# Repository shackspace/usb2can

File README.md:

usb2can
=======

Ein Adapter von USB auf CAn

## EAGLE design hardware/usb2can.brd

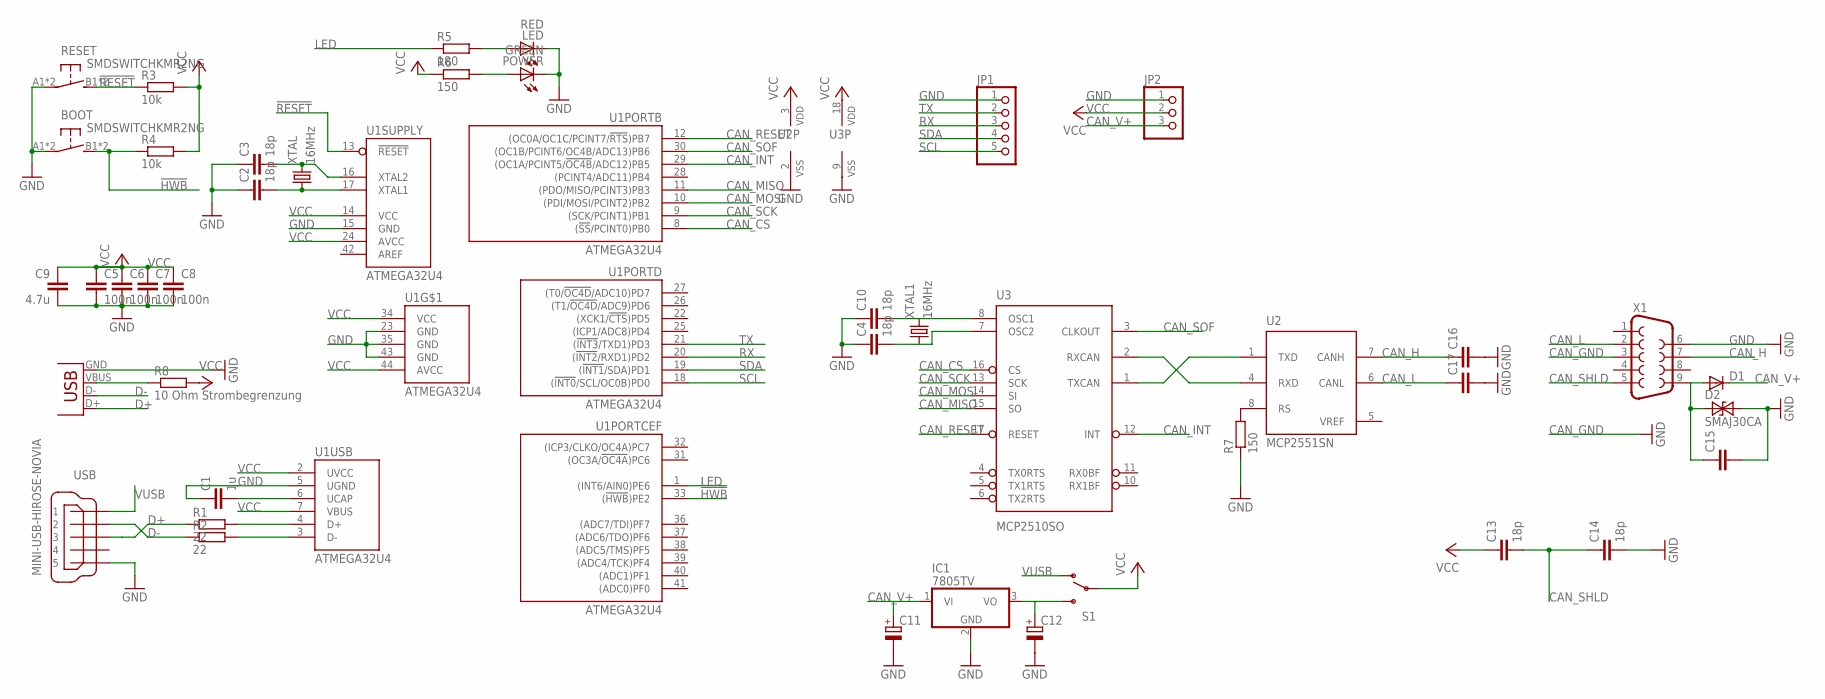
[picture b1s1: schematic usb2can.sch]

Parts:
BOOT: SMDSWITCHKMR2NG; KMR2NG
C1: 1u; C0603
C2, C3, C4, C10, C13, C14: 18p; C0603
C5, C6, C7, C8: 100n; C0603
C9: 4.7u; C0805K
C11, C12: CPOL-EU140CLH-1010; 140CLH-1010
C15, C16, C17: C-EUC0603; C0603
D1: DIODESOD; SOD-323
D2: SMAJ30CA; DO214AC
IC1: 7805TV; TO220V
JP1: PINHD-1X5; 1X05
JP2: PINHD-1X3; 1X03
LED: RED; CHIPLED_0805
POWER: GREEN; CHIPLED_0805
R1, R2: 22; R0603
R3, R4: 10k; R0603
R5: 180; R0603
R6, R7: 150; R0603
R8: 10 Ohm Strombegrenzung; R0603
RESET: SMDSWITCHKMR2NG; KMR2NG
S1: SWITCH-SPSTSMD2; SWITCH-SPDT-SMD
U1: ATMEGA32U4; TQFP44
U2: MCP2551SN; SO-08
U3: MCP2510SO; SO-18W
USB: MINI-USB-HIROSE-NOVIA; SMD-HIROSE-NOVIA
X1: F09D
X2: USB-A-S
XTAL, XTAL1: 16MHz; ABM7

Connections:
!HWB: BOOT.B1 (S), BOOT.B2 (S), R4.1, U1.33 ((!HWB!)PE2)
!RESET: R3.1, RESET.B1 (S), RESET.B2 (S), U1.13 (!RESET)
AREF: U1.42 (AREF)
CAN_CS: U1.8 ((!SS!/PCINT0)PB0), U3.16 (CS)
CAN_GND: X1.3
CAN_H: C16.1, U2.7 (CANH), X1.7
CAN_INT: U1.29 ((OC1A/PCINT5/!OC4B!/ADC12)PB5), U3.12 (INT)
CAN_L: C17.1, U2.6 (CANL), X1.2
CAN_MISO: U1.11 ((PDO/MISO/PCINT3)PB3), U3.15 (SO)
CAN_MOSI: U1.10 ((PDI/MOSI/PCINT2)PB2), U3.14 (SI)
CAN_RESET: U1.12 ((OC0A/OC1C/PCINT7/!RTS!)PB7), U3.17 (RESET)
CAN_SCK: U1.9 ((SCK/PCINT1)PB1), U3.13 (SCK)
CAN_SHLD: X1.5
CAN_SOF: U1.30 ((OC1B/PCINT6/OC4B/ADC13)PB6), U3.3 (CLKOUT)
CAN_V+: C11.+, D1.1 (C), IC1.1 (VI), JP2.3
D+: R1.1, USB.3, X2.D+
D-: R2.1, USB.2, X2.D-
GND: BOOT.A1, BOOT.A2, C1.1, C2.1, C3.1, C4.1, C5.2, C6.2, C7.2, C8.2, C9.2, C10.1, C11.-, C12.-, C14.2, C15.2, C16.2, C17.2, D2.2, IC1.2 (GND), JP1.1, JP2.1, LED.C, POWER.C, R7.1, RESET.A1, RESET.A2, U1.5 (UGND), U1.15 (GND), U1.23 (GND), U1.35 (GND), U1.43 (GND), U2.2 (VSS), U3.9 (VSS), USB.5, X1.6, X2.GND
LED: R5.1, U1.1 ((INT6/AIN0)PE6)
unnamed: R8.1, X2.VBUS
unnamed: C15.1, D1.2 (A), D2.1, X1.9
unnamed: C10.2, U3.8 (OSC1), XTAL1.P$2 (2)
unnamed: C2.2, U1.17 (XTAL1), XTAL.P$1 (1)
unnamed: C3.2, U1.16 (XTAL2), XTAL.P$2 (2)
unnamed: C1.2, U1.6 (UCAP)
unnamed: POWER.A, R6.2
unnamed: R1.2, U1.4 (D+)
unnamed: R2.2, U1.3 (D-)
unnamed: LED.A, R5.2
unnamed: C4.2, U3.7 (OSC2), XTAL1.P$1 (1)
unnamed: R7.2, U2.8 (RS)
unnamed: C12.+, IC1.3 (VO), S1.3 (S)
unnamed: C13.2, C14.1
unnamed: U2.4 (RXD), U3.2 (RXCAN)
unnamed: U2.1 (TXD), U3.1 (TXCAN)
RX: JP1.3, U1.20 ((!INT2!/RXD1)PD2)
SCL: JP1.5, U1.18 ((!INT0!/SCL/OC0B)PD0)
SDA: JP1.4, U1.19 ((!INT1!/SDA)PD1)
TX: JP1.2, U1.21 ((!INT3!/TXD1)PD3)
VCC: C5.1, C6.1, C7.1, C8.1, C9.1, C13.1, JP2.2, R3.2, R4.2, R6.1, R8.2, S1.2, U1.2 (UVCC), U1.7 (VBUS), U1.14 (VCC), U1.24 (AVCC), U1.34 (VCC), U1.44 (AVCC), U2.3 (VDD), U3.18 (VDD)
VREF: U2.5 (VREF)
VUSB: S1.1 (O), USB.1

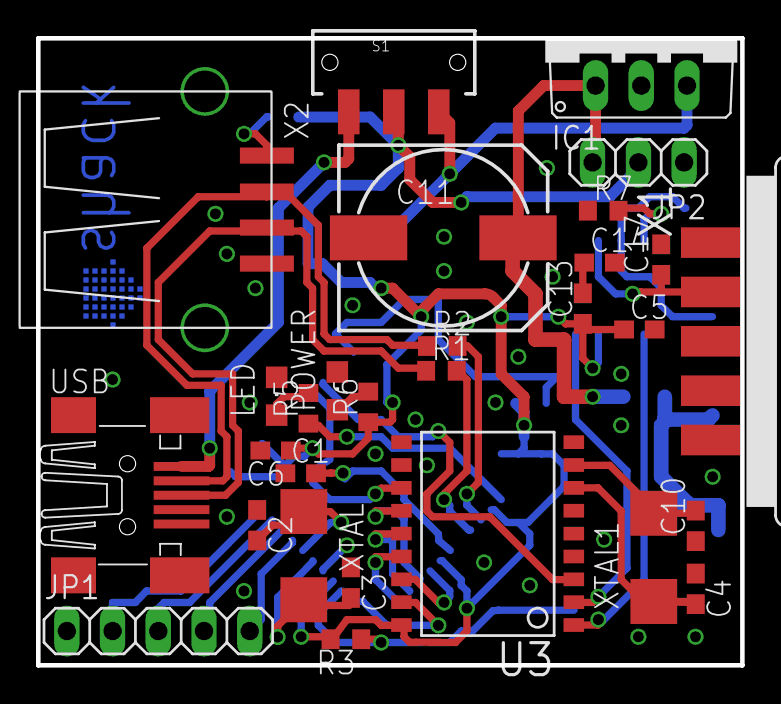
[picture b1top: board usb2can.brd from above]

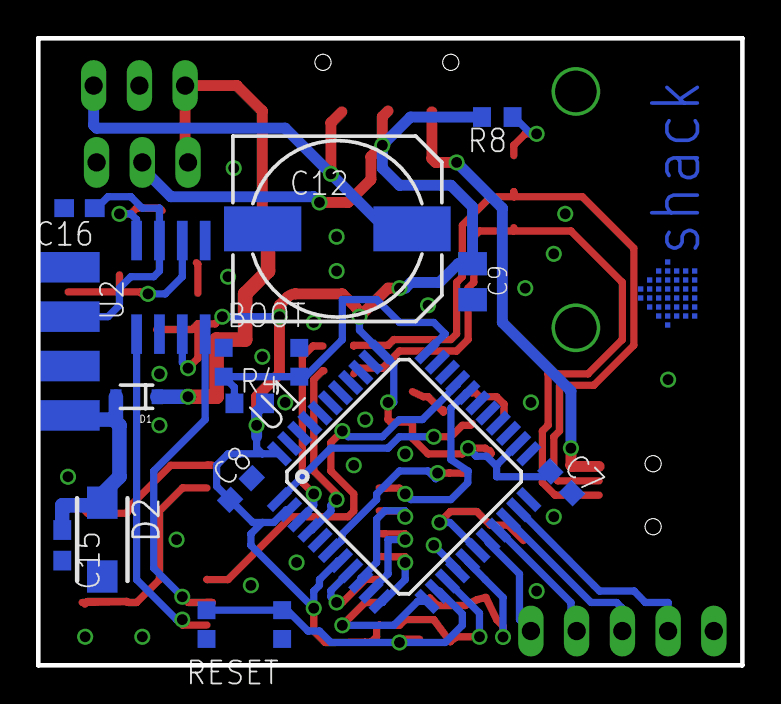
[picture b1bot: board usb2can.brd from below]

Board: 2 copper layers, 39.1 x 34.8 mm, 43 parts (14 on the bottom side), 38 nets.

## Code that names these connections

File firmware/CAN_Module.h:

#ifndef __CAN_H__
#define __CAN_H__

#include "lib/CAN/can.h"
#include "inttypes.h"
#ifndef TEST
#include <avr/io.h>
#include <avr/wdt.h>
#include <avr/interrupt.h>
#include <avr/power.h>
#endif

/** 
 * initialise the MCP2515, must be connected     to
 *   - PB0 ... not connected
 *   - PB1 ... CLK
 *   - PB2 ... MOSI
 *   - PB2 ... MISO
 *   - PB7 ... Connected to !RESET
 *   - PB0 ... Connected to !CS
 *   - PB5 ... Connected to CANINT
 */

#define ASCII_CAN_MESSAGE_LENGTH 24

#define MAX_BUFFER_LENGTH 128

#define CAN_ASCII_MESSAGE_BEGIN_CHAR 'I'
#define CAN_ASCII_MESSAGE_END_CHAR ';'

#ifdef __cplusplus
extern "C"
{
#endif

int CAN_Init();

void can2ascii(char* _string, can_t* _can);

bool ascii2can(char* _string, can_t* _can);

int ascii_message_exists(char* str);

void get_substring(char* src, char* dest, unsigned int begin, unsigned int end);

#ifdef __cplusplus
}
#endif

#endif

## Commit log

2012-11-18 started firmware
2012-11-18 deleted compiler generated file
2012-11-18 implemented can message to ascii converter
2012-11-18 removed compiler generated file
2012-11-19 implementing ascii to can message converter --> it compiles... but not tested
2012-11-19 edited usb device information
2012-11-23 communication between µC and can transciever is working implementing basic usb protocoll
2012-11-24 interpret ascii code on serial channel 2 and convert it to can get can message and output it on channel 2 as ascii
2012-12-02 added test case for CAN_Module
2012-12-02 added a lot of tests which make sure that conversation algorithms ascii<->can are working WIP: virtual serial port 0 interface, user interface and configuration WIP: virtual serial port 1 interface, 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
2012-12-02 sending "NOK" when ascii message was not correct
2012-12-05 implementing command interpreter
2012-12-05 added files EEPROM.h EEPROM.c
2012-12-05 added EEPROM to makefile, modified Interpreter
2012-12-24 resolved a bug in getline
2012-12-24 preparing saving the settings in EEPROM
2012-12-28 added the CAN Start of Frame signal path to pcb
2012-12-28 solving a lot of bugs
2013-01-01 added some debug features
2013-01-03 changed CAN_ASCII_MESSAGE_CHAR from \n to ;
2013-01-03 conversation of ascii stream to can message on channel 2 now possible

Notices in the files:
parts and their libraries:
SparkFun: Licensing: CC v3.0 Share-Alike You are welcome to use this library for commercial purposes.
